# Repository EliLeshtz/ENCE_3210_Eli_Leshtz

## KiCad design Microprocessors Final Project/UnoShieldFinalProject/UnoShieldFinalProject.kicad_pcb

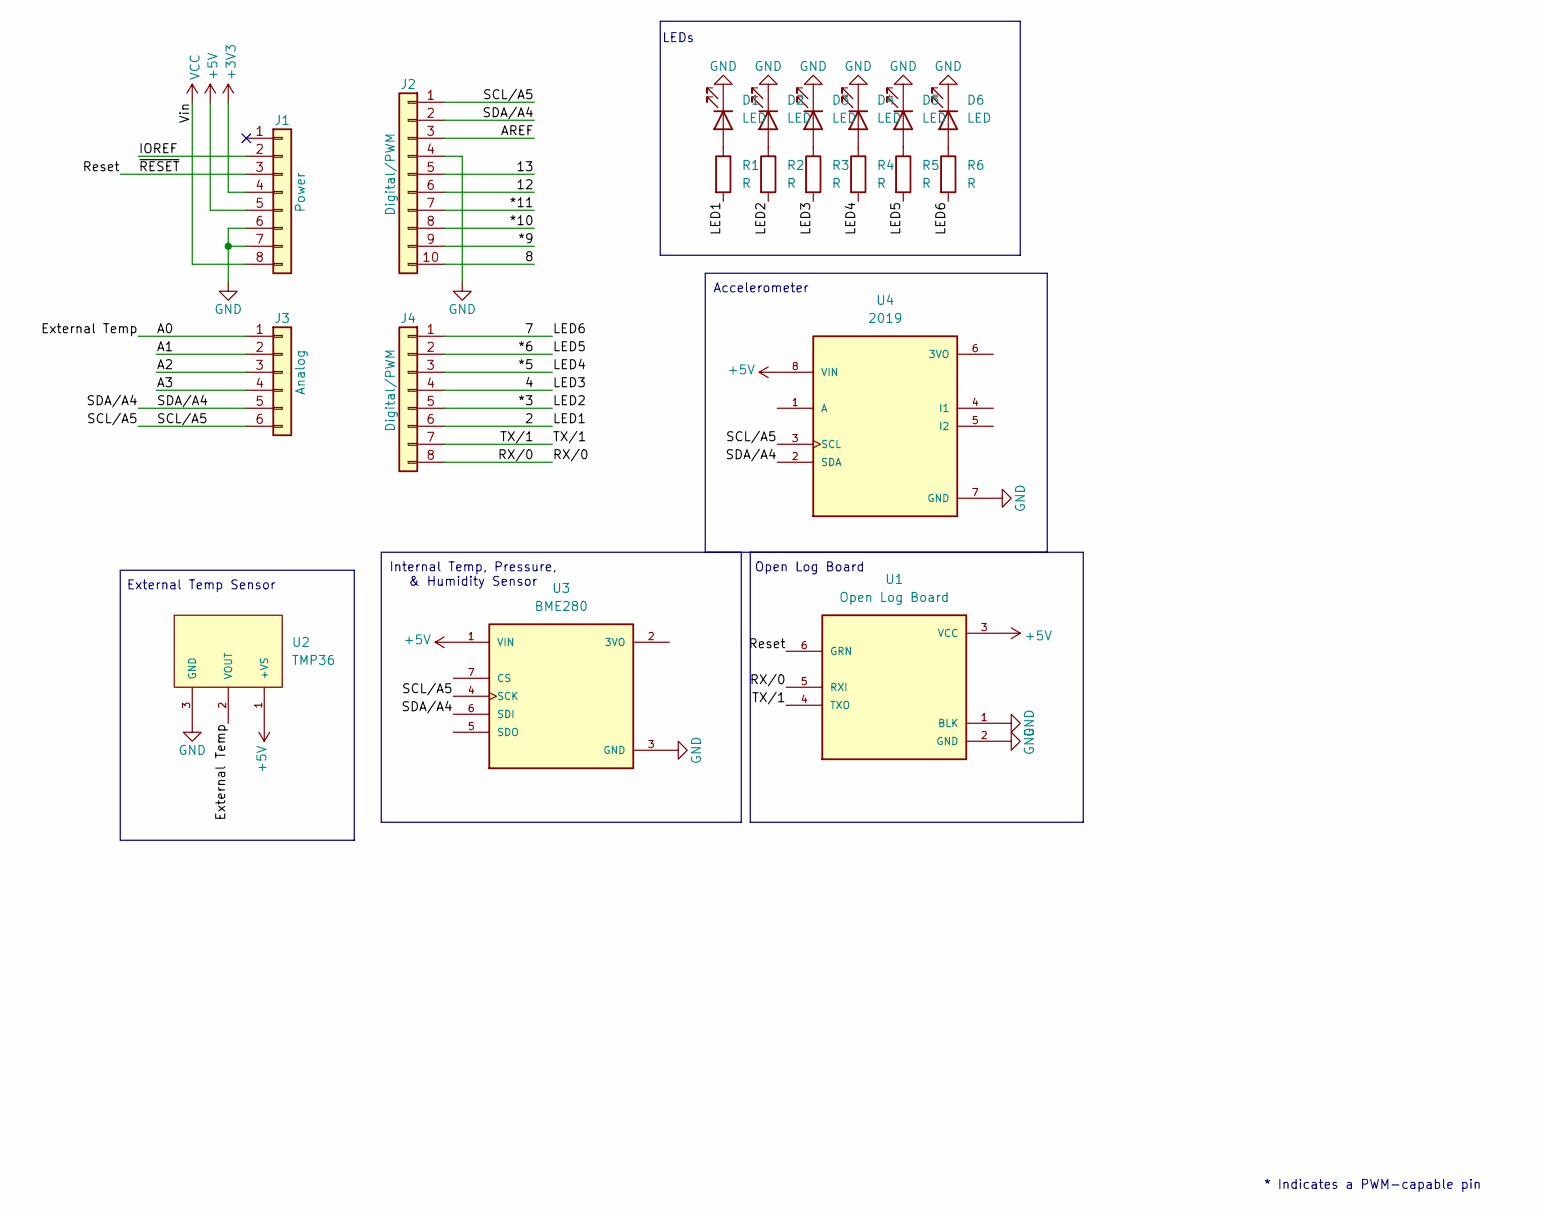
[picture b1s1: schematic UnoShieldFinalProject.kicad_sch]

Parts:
D1, D2, D3, D4, D5, D6: LED; LED_D5.0mm
J1: Power; PinSocket_1x08_P2.54mm_Vertical
J2: Digital/PWM; PinSocket_1x10_P2.54mm_Vertical
J3: Analog; PinSocket_1x06_P2.54mm_Vertical
J4: Digital/PWM; PinSocket_1x08_P2.54mm_Vertical
R1, R2, R3, R4, R5, R6: R; R_Axial_DIN0411_L9.9mm_D3.6mm_P12.70mm_Horizontal
U1: Open Log Board; MODULE_DEV-13712; PARTREV v15
U2: TMP36; TO92127P521H733-3; PARTREV H
U3: BME280; MODULE_2652; PARTREV N/A
U4: 2019; MODULE_2019; PARTREV 2021-11-15

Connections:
+3V3: J1.4
+5V: J1.5, U1.3 (VCC), U2.1 (+VS), U3.1 (VIN), U4.8 (VIN)
/2: J4.6, R1.2
/4: J4.4, R3.2
/7: J4.1, R6.2
/8: J2.10
/12: J2.6
/13: J2.5
/*3: J4.5, R2.2
/*5: J4.3, R4.2
/*6: J4.2, R5.2
/*9: J2.9
/*10: J2.8
/*11: J2.7
/A0: J3.1, U2.2 (VOUT)
/A1: J3.2
/A2: J3.3
/A3: J3.4
/AREF: J2.3
/IOREF: J1.2
/RX/0: J4.8, U1.5 (RXI)
/Reset: J1.3, U1.6 (GRN)
/SCL/A5: J2.1, J3.6, U3.4 (SCK), U4.3 (SCL)
/SDA/A4: J2.2, J3.5, U3.6 (SDI), U4.2 (SDA)
/TX/1: J4.7, U1.4 (TXO)
GND: D1.1 (K), D2.1 (K), D3.1 (K), D4.1 (K), D5.1 (K), D6.1 (K), J1.6, J1.7, J2.4, U1.1 (BLK), U1.2 (GND), U2.3 (GND), U3.3 (GND), U4.7 (GND)
unnamed: D1.2 (A), R1.1
unnamed: D2.2 (A), R2.1
unnamed: D3.2 (A), R3.1
unnamed: D4.2 (A), R4.1
unnamed: D5.2 (A), R5.1
unnamed: D6.2 (A), R6.1
VCC: J1.8

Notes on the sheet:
Internal Temp, Pressure, & Humidity Sensor
Open Log Board
Accelerometer
LEDs
External Temp Sensor
* Indicates a PWM-capable pin

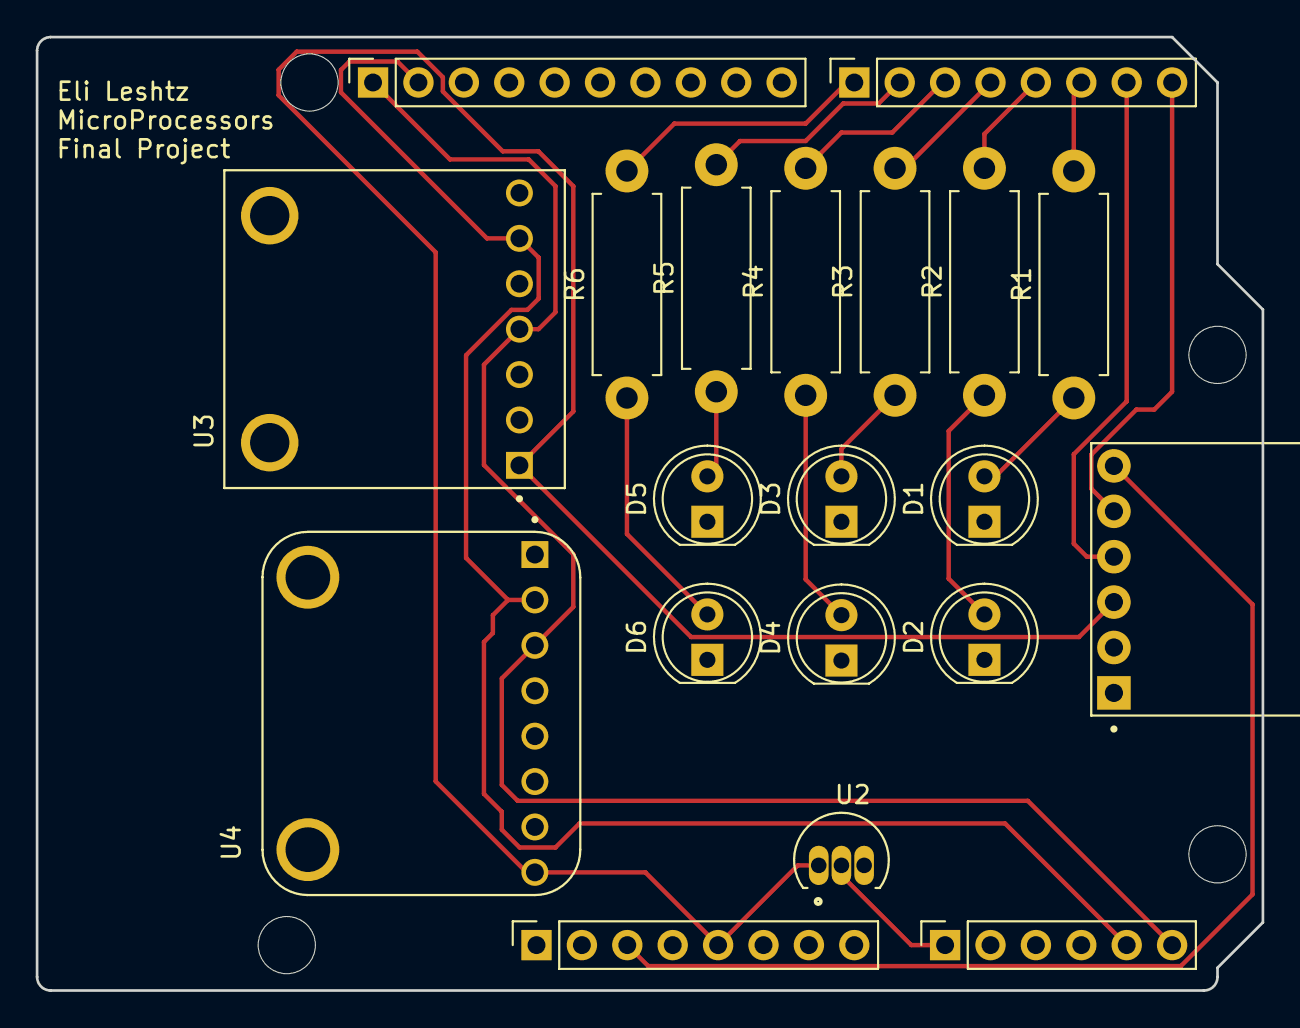
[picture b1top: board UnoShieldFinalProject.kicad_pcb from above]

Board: 2 copper layers, 68.6 x 53.3 mm, 24 parts (0 on the bottom side), 20 nets.

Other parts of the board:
MH1, MH2, MH3, MH4: MountingHole_3.2mm

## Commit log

2025-01-10 V1.0
2025-01-17 v2.0
